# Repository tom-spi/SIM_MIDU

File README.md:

# SIM_MIDU
Re-purposing an AlliedSignal Avionics 747 MIDU unit for an A300-600F based flight simualtor. Will interface with XP11. Utilizing original display (LQ4RA01), and front panel. Most likely will be FPGA based.

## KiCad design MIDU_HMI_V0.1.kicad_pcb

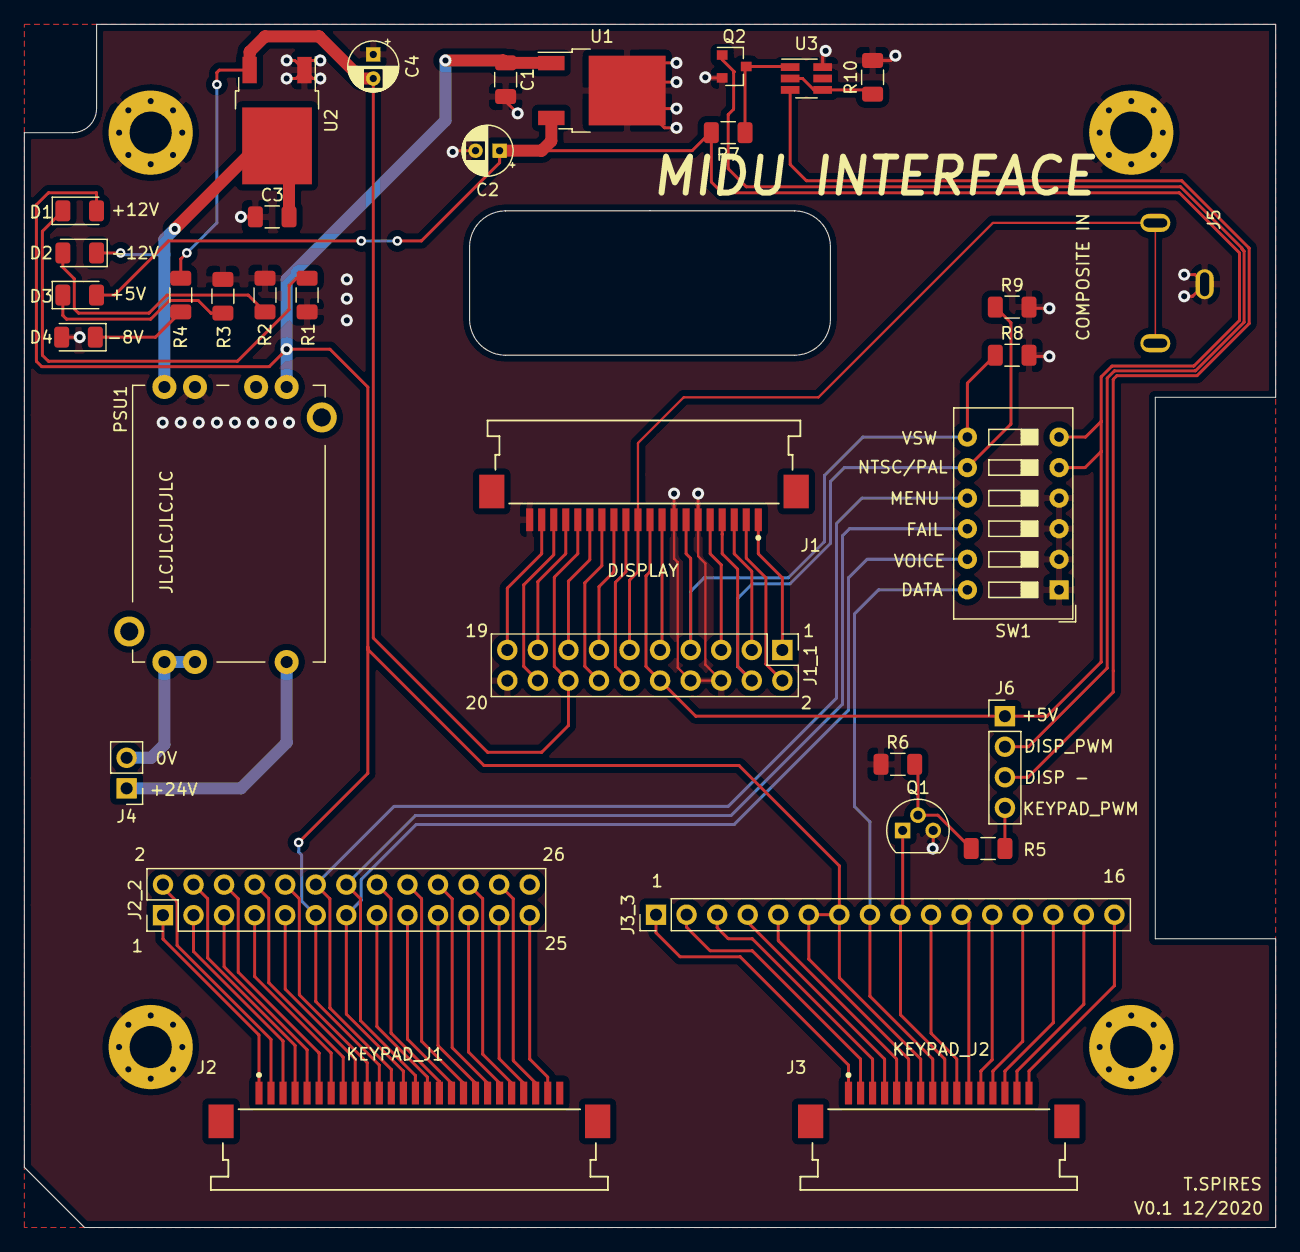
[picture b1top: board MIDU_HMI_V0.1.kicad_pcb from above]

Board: 2 copper layers, 104.0 x 100.0 mm, 38 parts (0 on the bottom side), 69 nets.

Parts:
C1, C3: 0.33uF; C_1206_3216Metric
C2, C4: 4.7uF; CP_Radial_D4.0mm_P2.00mm
D1, D2, D3, D4: LED_ALT; LED_1206_3216Metric
J1: LCD_Module; Molex-52207-2033-Manufacturer_Recommended
J1_1: Display_Pin; PinHeader_2x10_P2.54mm_Vertical
J2: KEYPAD_J1; Molex-52271-2679-Manufacturer_Recommended
J2_2: KEYPAD_PIN_J1; PinHeader_2x13_P2.54mm_Vertical
J3: KEYPAD_J2; Molex-52271-1679-Manufacturer_Recommended
J3_3: KEYPAD_PIN_J2; PinHeader_1x16_P2.54mm_Vertical
J4: Screw_Terminal_01x02; PinHeader_1x02_P2.54mm_Vertical
J5: COMP_VIDEO_IN; RCA
J6: LCD_BLIGHT_PWM; PinHeader_1x04_P2.54mm_Vertical
PSU1: CC-3-2412DF-E; CC3-xxxxxF-E
Q1: 2N2222A; TO-92
Q2: DDTC144ECA-7-F; SOT-23
R1: e; R_1206_3216Metric
R2, R3, R4: R; R_1206_3216Metric
R5, R6: 1K; R_1206_3216Metric
R7: 12K; R_1206_3216Metric
R8, R9: 10K; R_1206_3216Metric
R10: 28R; R_1206_3216Metric
SW1: SW_DIP_x06; SW_DIP_SPSTx06_Slide_9.78x17.42mm_W7.62mm_P2.54mm
U1: L7805; TO-252-2
U2: MC79M08_TO252; TO-252-2
U3: AL5801; SOT-23-6_Handsoldering
e: MountingHole_3.5mm_Pad_Via
e#2, e#3, e#4: MountingHole_3.5mm_Pad_Via

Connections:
+5V: C2.1, D3.2, J1.10, J1_1.10, J6.1, R7.2, SW1.5, SW1.6, U1.3
+12V: C1.1, D1.2, J2.11, J2_2.11, J3.6, J3.7, J3_3.6, J3_3.7, PSU1.7, U1.1
-8V: C4.2, J1.16, J1_1.16, R4.2, U2.3
-12V: C3.2, D2.1, PSU1.4, U2.2
/BACKLIGHT_PWM_DISPLAY: J6.2, Q2.1
/BRT: J1.12, J1_1.12
/DATA_LED-: J3.8, J3_3.8, SW1.12
/DISPLAY_BACKLIGHT-: J6.3, U3.3
/FAIL_LED-: J2.14, J2_2.14, SW1.10
/HSYNC: J1.1, J1_1.1
/KEYPAD_1: J2.1, J2_2.1
/KEYPAD_2: J2.2, J2_2.2
/KEYPAD_3: J2.3, J2_2.3
/KEYPAD_4: J2.4, J2_2.4
/KEYPAD_5: J2.5, J2_2.5
/KEYPAD_6: J2.6, J2_2.6
/KEYPAD_7: J2.7, J2_2.7
/KEYPAD_8: J2.8, J2_2.8
/KEYPAD_9: J2.9, J2_2.9
/KEYPAD_15: J2.15, J2_2.15
/KEYPAD_16: J2.16, J2_2.16
/KEYPAD_17: J2.17, J2_2.17
/KEYPAD_18: J2.18, J2_2.18
/KEYPAD_19: J2.19, J2_2.19
/KEYPAD_20: J2.20, J2_2.20
/KEYPAD_21: J2.21, J2_2.21
/KEYPAD_22: J2.22, J2_2.22
/KEYPAD_23: J2.23, J2_2.23
/KEYPAD_24: J2.24, J2_2.24
/KEYPAD_25: J2.25, J2_2.25
/KEYPAD_BACKLIGHT-: J2.10, J2_2.10, J3.9, J3_3.9, Q1.1
/KEYPAD_BACKLIGHT_PWM: J6.4, R5.2
/MENU_LED-: J2.12, J2_2.12, SW1.9
/NTSC-PAL: J1.4, J1_1.4, R9.1, SW1.8
/TST1: J1.3, J1_1.3
/TST2: J1.5, J1_1.5
/VB1: J1.15, J1_1.15
/VB2: J1.19, J1_1.19
/VBS: J1.11, J1_1.11, J5.1
/VCDC: J1.9, J1_1.9
/VG1: J1.14, J1_1.14
/VG2: J1.18, J1_1.18
/VOICE_LED-: J2.13, J2_2.13, SW1.11
/VR1: J1.13, J1_1.13
/VR2: J1.17, J1_1.17
/VSW: J1.7, J1_1.7, R8.1, SW1.7
/VSYNC: J1.2, J1_1.2
GND: C1.2, C2.2, C3.1, C4.1, D4.2, J1.6, J1.8, J1.20, J1_1.6, J1_1.8, J1_1.20, J5.2, PSU1.5, Q1.3, Q2.2, R1.2, R2.2, R3.1, R6.1, R8.2, R9.2, R10.2, SW1.1, SW1.2, SW1.3, SW1.4, U1.2, U2.1, U3.6, e.1, e#2.1, e#3.1, e#4.1
unnamed: D1.1, R1.1
unnamed: D2.2, R2.1
unnamed: D3.1, R3.2
unnamed: D4.1, R4.1
unnamed: J3.1, J3_3.1
unnamed: J3.2, J3_3.2
unnamed: J3.3, J3_3.3
unnamed: J3.4, J3_3.4
unnamed: J3.5, J3_3.5
unnamed: J3.10, J3_3.10
unnamed: J3.11, J3_3.11
unnamed: J3.12, J3_3.12
unnamed: J3.13, J3_3.13
unnamed: J3.14, J3_3.14
unnamed: J3.15, J3_3.15
unnamed: J3.16, J3_3.16
unnamed: J4.1, PSU1.1
unnamed: J4.2, PSU1.2, PSU1.3
unnamed: Q1.2, R5.1, R6.2
unnamed: Q2.3, R7.1, U3.1
unnamed: R10.1, U3.2, U3.4
